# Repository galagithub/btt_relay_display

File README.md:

## BTT Relay Display

A small PCB that can display the status of the relay, it connects to it through a 5 pin cable. A reset switch is also provided.
You can also program/flash the relay through it, there is a separate header for programmer connection.

### Related projects
- BTT Relay v1.2 https://github.com/bigtreetech/BIGTREETECH-Relay-V1.2
- Custom firmware with platform.io https://github.com/galagithub/btt_relay_os

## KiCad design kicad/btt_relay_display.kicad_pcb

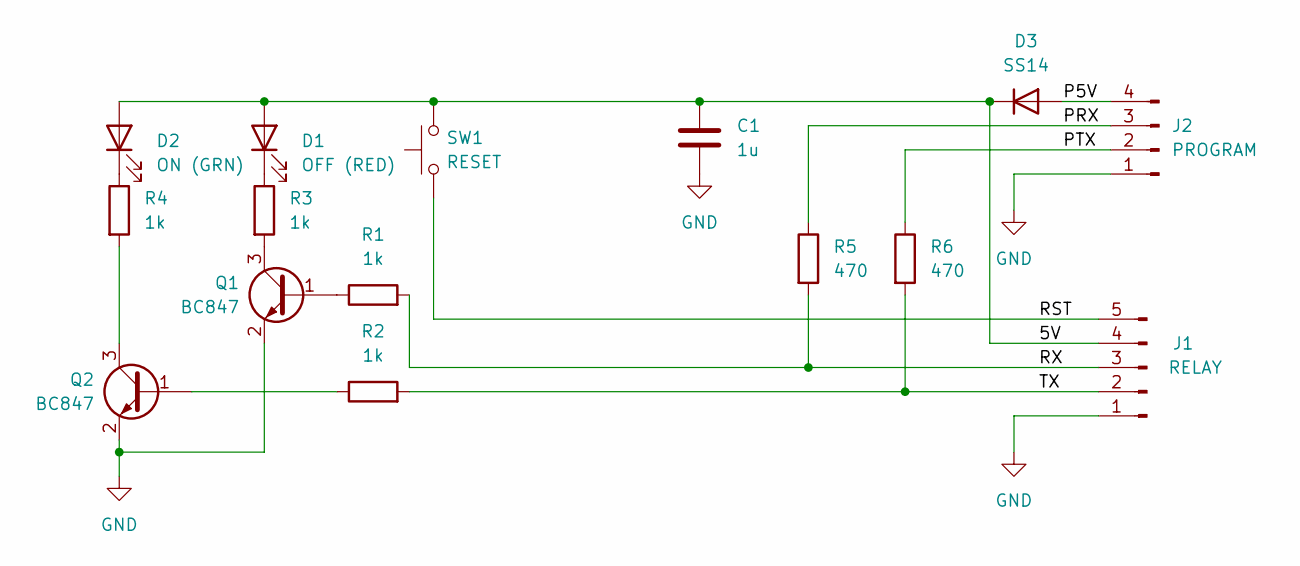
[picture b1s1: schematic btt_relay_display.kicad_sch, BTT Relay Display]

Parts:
C1: 1u; C_0805_2012Metric
D1: OFF (RED); LED_D3.0mm
D2: ON (GRN); LED_D3.0mm
D3: SS14; D_SMA
J1: RELAY; PinHeader_1x05_P2.54mm_Vertical
J2: PROGRAM; PinHeader_1x04_P2.54mm_Vertical
Q1, Q2: BC847; SOT-23
R1, R2, R3, R4: 1k; R_0805_2012Metric
R5, R6: 470; R_0805_2012Metric
SW1: RESET; SW_PUSH_6mm_H5mm

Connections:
/5V: C1.1, D1.2 (A), D2.2 (A), D3.1 (K), J1.4, SW1.1
/P5V: D3.2 (A), J2.4
/PRX: J2.3, R5.1
/PTX: J2.2, R6.1
/RST: J1.5, SW1.2
/RX: J1.3, R1.2, R5.2
/TX: J1.2, R2.2, R6.2
GND: C1.2, J1.1, J2.1, Q1.2 (E), Q2.2 (E)
unnamed: D1.1 (K), R3.1
unnamed: D2.1 (K), R4.1
unnamed: Q1.1 (B), R1.1
unnamed: Q1.3 (C), R3.2
unnamed: Q2.1 (B), R2.1
unnamed: Q2.3 (C), R4.2

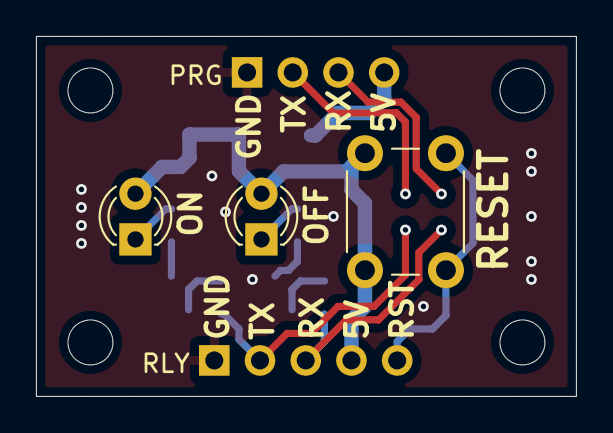
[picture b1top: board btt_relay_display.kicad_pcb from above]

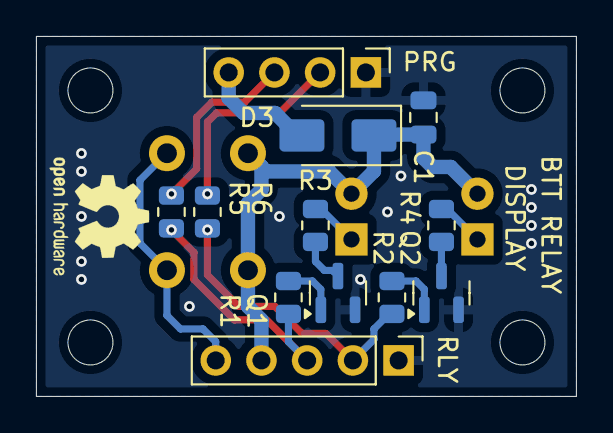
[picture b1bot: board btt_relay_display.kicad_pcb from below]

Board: 2 copper layers, 30.0 x 20.0 mm, 15 parts (12 on the bottom side), 14 nets.

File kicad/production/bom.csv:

Designator,Footprint,Quantity,Value,LCSC Part #
C1,0805,1,1u,
D1,LED_D3.0mm,1,OFF (RED),
D2,LED_D3.0mm,1,ON (GRN),
D3,D_SMA,1,SS14,
J1,PinHeader_1x05_P2.54mm_Vertical,1,RELAY,
J2,PinHeader_1x04_P2.54mm_Vertical,1,PROGRAM,
"Q1, Q2",SOT-23,2,BC847,
"R1, R2, R3, R4",0805,4,1k,
"R5, R6",0805,2,470,
SW1,SW_PUSH_6mm_H5mm,1,RESET,

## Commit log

2024-12-07 Add stl dir
2024-12-07 Update PCB to include OHW logo and position reference text properly.
2024-12-07 Add small description in README
2024-12-07 Typos
2024-12-07 Add related projects in readme
2024-12-07 Add rendered pictures of PCB
2024-12-07 show top pcb render in readme
2024-12-08 Holes made 2.5mm add pcb name text, generate gerbes for jlcpcb assembly service
2024-12-08 PCB v1 stl export
2024-12-08 Remove rogue file locks
2024-12-09 Initial front face for mounting box, just source.
2024-12-09 Initial front face for mounting box, the stl
2024-12-10 Update front face stl design, to be tested.

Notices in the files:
kicad/btt_relay_display.kicad_sch:
﻿CERN Open Hardware Licence v1.2
